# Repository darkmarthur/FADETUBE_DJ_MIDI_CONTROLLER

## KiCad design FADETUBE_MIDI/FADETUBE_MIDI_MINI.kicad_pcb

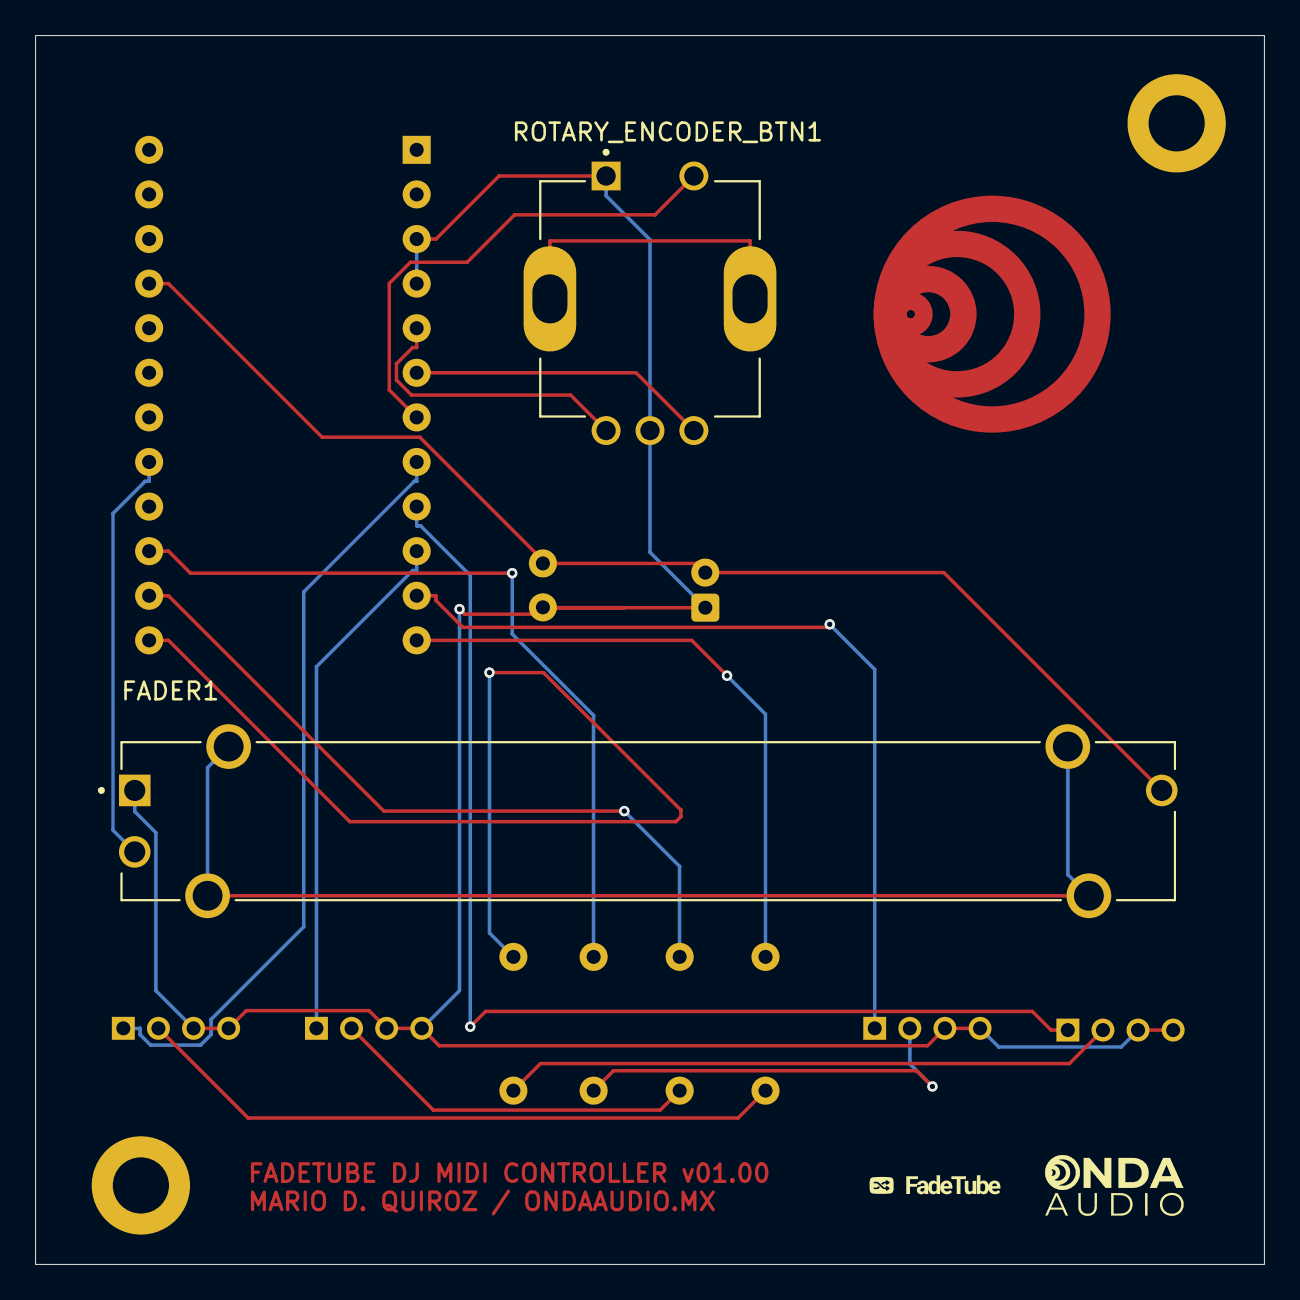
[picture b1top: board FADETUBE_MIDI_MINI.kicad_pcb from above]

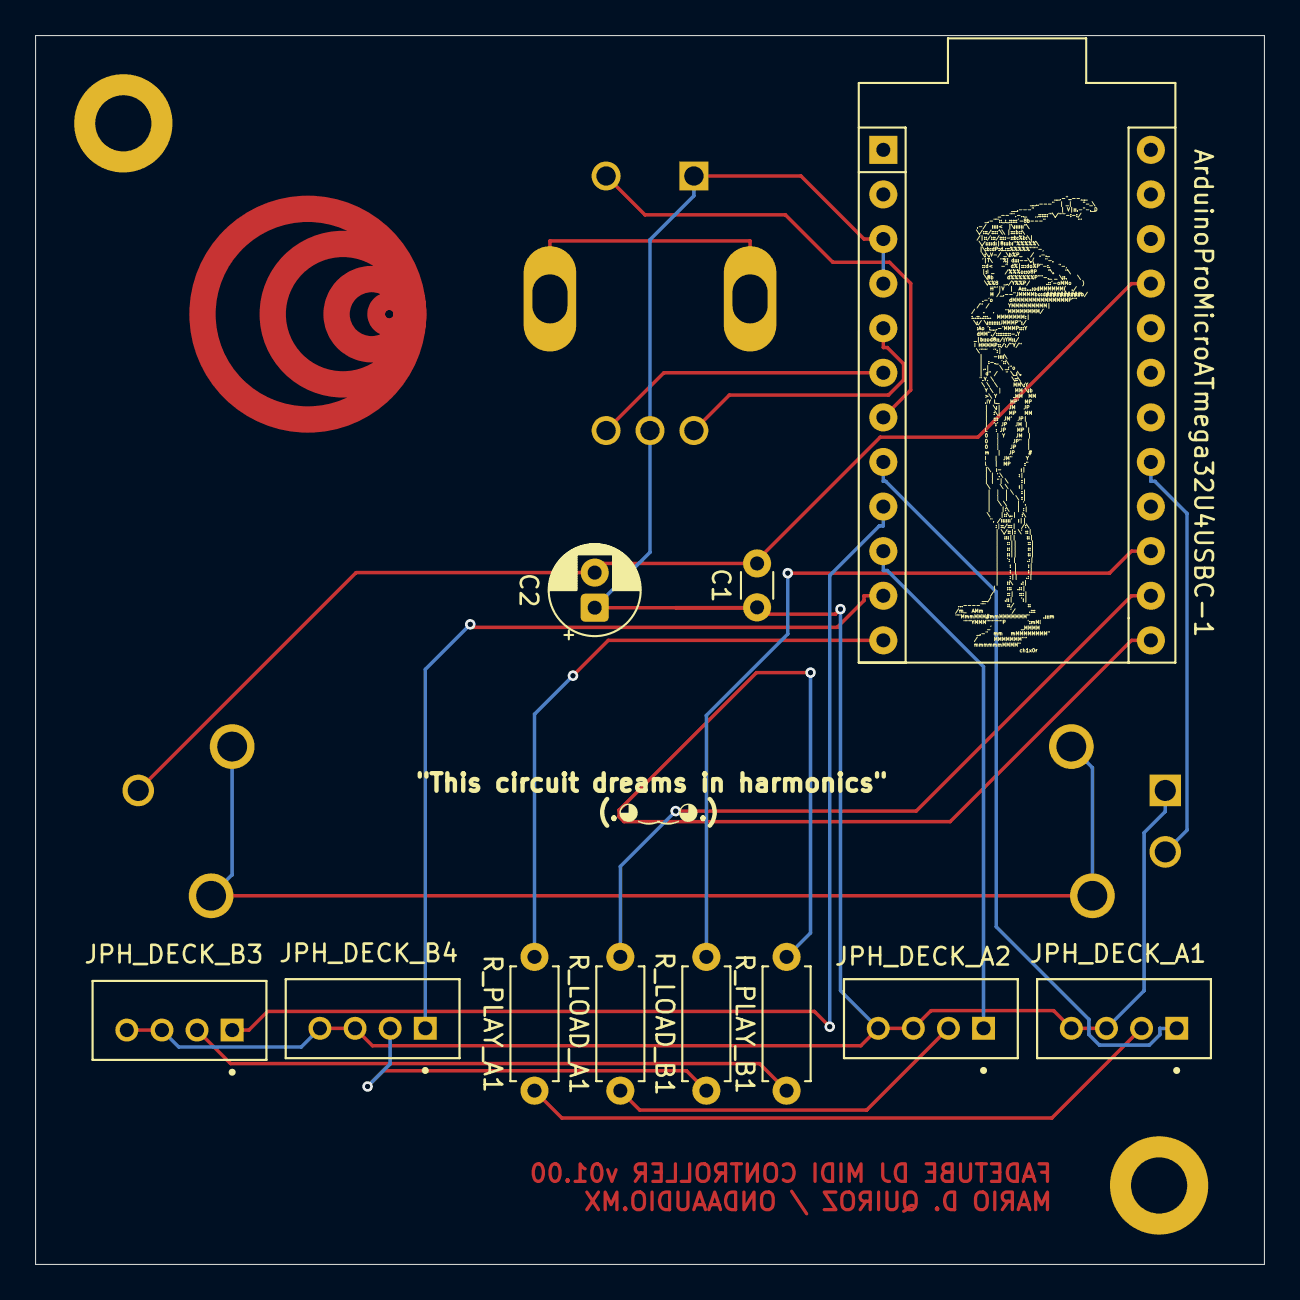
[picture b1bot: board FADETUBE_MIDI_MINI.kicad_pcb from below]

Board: 2 copper layers, 70.0 x 70.0 mm, 17 parts (11 on the bottom side), 20 nets.

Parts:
ArduinoProMicroATmega32U4USBC-1: SPARKFUN QWIIC PRO MICRO - USB-C; Sparkfun_Pro_Micro
C1: 0.1 µF; C_Disc_D3.0mm_W1.6mm_P2.50mm
C2: 10 µF; CP_Radial_D5.0mm_P2.00mm
FADER1: PTA4553-2215CIB103 10k 45mm; TRIM_PTA4553-2215CIB103
FADETUBE-LOGO: LOGO; fadetube-logo
JPH_DECK_A1, JPH_DECK_A2: B4B-PH-K-S; JST_B4B-PH-K-S
JPH_DECK_B3, JPH_DECK_B4: B4B-PH-K-S; JST_B4B-PH-K-S
MH1, MH2: MountingHole_3.2mm_M3_DIN965_Pad
ONDAAUDIO-LOGO: LOGO; onda-audio-logo
ROTARY_ENCODER_BTN1: PEC11R-4220K-S0024 10k; XDCR_PEC11R-4220K-S0024
R_LOAD_A1: 470 Ohms; R_Axial_DIN0207_L6.3mm_D2.5mm_P7.62mm_Horizontal
R_LOAD_B1: 470 Ohms; R_Axial_DIN0207_L6.3mm_D2.5mm_P7.62mm_Horizontal
R_PLAY_A1: 470 Ohms; R_Axial_DIN0207_L6.3mm_D2.5mm_P7.62mm_Horizontal
R_PLAY_B1: 470 Ohms; R_Axial_DIN0207_L6.3mm_D2.5mm_P7.62mm_Horizontal

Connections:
GND: ArduinoProMicroATmega32U4USBC-1.3 (GND), ArduinoProMicroATmega32U4USBC-1.4 (GND), C1.1, C2.1, FADER1.1, JPH_DECK_A1.3, JPH_DECK_A1.4, JPH_DECK_A2.3, JPH_DECK_A2.4, JPH_DECK_B3.3, JPH_DECK_B3.4, JPH_DECK_B4.3, JPH_DECK_B4.4, ROTARY_ENCODER_BTN1.1, ROTARY_ENCODER_BTN1.C (COM)
unnamed: ArduinoProMicroATmega32U4USBC-1.5 (D2), ROTARY_ENCODER_BTN1.A
unnamed: ArduinoProMicroATmega32U4USBC-1.7 (D4/A6), ROTARY_ENCODER_BTN1.2
unnamed: ArduinoProMicroATmega32U4USBC-1.10 (D7), JPH_DECK_A2.1
unnamed: ArduinoProMicroATmega32U4USBC-1.11 (D8/A8), JPH_DECK_B4.1
unnamed: ArduinoProMicroATmega32U4USBC-1.15 (D14), R_LOAD_B1.2
unnamed: ArduinoProMicroATmega32U4USBC-1.14 (D16), R_LOAD_A1.2
unnamed: ArduinoProMicroATmega32U4USBC-1.17 (D18/A0), FADER1.2
unnamed: ArduinoProMicroATmega32U4USBC-1.21 (VCC), C1.2, C2.2, FADER1.3
unnamed: ArduinoProMicroATmega32U4USBC-1.6 (~D3), ROTARY_ENCODER_BTN1.B
unnamed: ArduinoProMicroATmega32U4USBC-1.8 (~D5), JPH_DECK_A1.1
unnamed: ArduinoProMicroATmega32U4USBC-1.9 (~D6/A7), JPH_DECK_B3.1
unnamed: ArduinoProMicroATmega32U4USBC-1.12 (~D9/A9), R_PLAY_A1.2
unnamed: ArduinoProMicroATmega32U4USBC-1.13 (~D10/A10), R_PLAY_B1.2
unnamed: FADER1.SH1 (SHIELD), FADER1.SH2 (SHIELD), FADER1.SH3 (SHIELD), FADER1.SH4 (SHIELD)
unnamed: JPH_DECK_A1.2, R_PLAY_A1.1
unnamed: JPH_DECK_A2.2, R_LOAD_A1.1
unnamed: JPH_DECK_B3.2, R_PLAY_B1.1
unnamed: JPH_DECK_B4.2, R_LOAD_B1.1
unnamed: ROTARY_ENCODER_BTN1.SH1 (SHIELD), ROTARY_ENCODER_BTN1.SH2 (SHIELD)

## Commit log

2026-01-15 INIT
2026-01-20 restructure project
2026-01-20 test smd
2026-01-20 capacitors
2026-01-20 MULTIPCB
2026-01-21 MVP PRIOR MANUFACTURING
2026-01-21 BOMLIST INCLUDED
2026-01-22 mvp tes pcbway and jlc
2026-01-23 add blender file
2026-01-27 ADVANCDED VERTION
2026-01-27 updated pcb
2026-02-10 3d Models
2026-02-11 Mods_10-02-26
2026-02-11 3d Updates
2026-02-12 new updates
2026-02-19 fix breath effect
2026-02-20 fader resiliency
